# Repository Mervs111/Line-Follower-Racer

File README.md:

# Line Follower ESP32 + Block Programming

Proyek PjBL Semester 5: robot line follower edukasi yang murah tapi performanya bagus, dan bisa diprogram pakai
blok (user extension Mind+). Target lomba: IARC XII Smart Robotics (9–10/01/2027). Anggaran maks Rp1.000.000 (naik dari Rp900.000 pada 26/10/2026).

> **Untuk anggota kelompok:** baca bagian [Status terkini](#status-terkini-23102026) dan
> [Yang harus dilakukan](#yang-harus-dilakukan-berikutnya) dulu. Catatan kerja harian ada di
> [`docs/log-kerja.md`](docs/log-kerja.md); detail rancangan lengkap (pin map, keputusan, aturan) di
> [`CLAUDE.md`](CLAUDE.md).

## Status terkini (23/10/2026)

| Bagian | Status | Di mana |
|---|---|---|
| Charter & RAB | Charter sudah disesuaikan dengan rancangan terbaru. **RAB Rp937.390 (harga hasil validasi marketplace 27/10), sisa Rp62.610** dari batas Rp1.000.000 | `docs/charter.md`, `docs/Project_Charter_PJBL.docx` |
| Diagram (blok, wiring, arsitektur, flowchart) | Selesai, sudah sesuai rancangan 22/10 | tautan di bawah, `docs/wiring-diagram.html` |
| PCB sensor | **Rev B disetujui**: bentuk jangkar, lebar 95 mm, 12 QRE1113GR + mux CD74HC4067, DRC 0 | `hardware/sensor-garis/` (+ `REVISI.md`) |
| Skematik PCB utama | **Selesai**: 21 komponen, ERC 0, netlist dicek terhadap pin map | `hardware/pcb-utama/pcb-utama.kicad_sch`, PDF `pcb-utama-skematik.pdf` |
| Layout PCB utama | **Routing pertama selesai** (22/10): bentuk "mobil F1" 100 × 127 mm, semua net tersambung, GND pour 2 sisi. Masih ada 11 error DRC dari footprint Q1 dan SW1 (lihat di bawah) | `hardware/pcb-utama/` (+ `README.md`) |
| Mekanik | Model 3D **v16**: PCB sensor rev B + PCB utama F1, 0 tabrakan. Body 3D print belum masuk RAB | `mechanical/` |
| Firmware | **Belum mulai** (M0). `Pins.h` dan `platformio.ini` masih untuk ESP32-S3 lama | `firmware/` |
| Extension Mind+ | Belum mulai (M6) | `mindplus-ext/` |

### Lihat hasilnya (artifact claude.ai)

- Model 3D v16 (bisa diputar): https://claude.ai/artifact/C6BMXLgUPLJN5Aubm8uyx3
- Perbandingan opsi bentuk PCB utama: https://claude.ai/artifact/PYASQTHgLPKjVaxw33yyMZ
- Wiring diagram per blok: https://claude.ai/artifact/Enb11oGXVb5YkwQmU6DhJY
- Diagram blok sistem: https://claude.ai/artifact/VgPaH3FbRFSDaHB658YTcT
- Arsitektur sistem: https://claude.ai/artifact/9dNV7sB3TdaNBcSojbtzAa · Flowchart: https://claude.ai/artifact/EMfY1GGrPrx9etNHpKmhEi

Artifact bersifat privat. Kalau link tidak bisa dibuka, minta pemiliknya membagikan lewat menu Share. Render
gambar model juga ada di `mechanical/render/`.

## Yang harus dilakukan berikutnya

Urut dari yang paling mendesak. Batas waktu dari pedoman PjBL dan charter: desain mekanik selesai **minggu 8**,
PCB dipesan **paling lambat minggu 10**, prototipe jalan 3× berturut-turut untuk **G3 (minggu 10)**.

### 1. Keputusan kelompok (perlu dibahas dulu)

- [x] ~~Pangkas RAB Rp2.000~~: tidak perlu lagi, batas anggaran naik jadi Rp1.000.000 (26/10).
- [ ] **Ukuran PCB utama**: tetap 100 × 127 mm, atau dipadatkan (OLED ditumpuk di atas ESP32, hidung dipendekkan,
      resistor SMD; perkiraan 15–25 % lebih kecil). Mengganti 18650 dengan LiPo bisa membuat papan jauh lebih kecil,
      tapi bertentangan dengan alasan keselamatan di charter, jadi tanyakan dosen dulu.
- [ ] **Saklar SW1**: pad pemasangnya berjarak 0,25 mm dari pad lain (batas tempat cetak 0,254 mm). Pilihannya:
      pelanggaran ini dikecualikan di DRC, atau ganti saklar.
- [x] ~~Skid nilon~~: diganti **ball caster** (RAB 27/10). Model 3D v16 masih memakai skid, perlu diperbarui.

### 2. PCB utama (sampai siap pesan)

- [ ] Ganti footprint Q1 ke `Package_TO_SOT_THT:TO-92_Inline_Wide` di Eeschema, lalu F8 di PCB Editor. Jangan
      jalankan ulang `gen_sch_utama.py` karena UUID-nya acak dan akan mengacak penempatan.
- [ ] Rapikan jalur Q1 ↔ R3/R4/buzzer, jalur daya (BAT+ masih melintang miring di B.Cu), dan silkscreen yang bertumpuk.
- [ ] **Cocokkan footprint modul dengan modul yang dibeli** (ESP32 DevKit, TB6612, MP1584 di `hardware/ltm-lib/`).
      Ukur jarak pin modul asli pakai jangka sorong; footprint sekarang masih perkiraan.
- [ ] **Footprint ikut barang di RAB 27/10**: tombol SW2/SW3 → tactile 12×12 mm (sekarang `SW_PUSH_6mm`), konektor
      motor J2/J3 → JST XH 6 pin `B6B-XH-A` (sekarang JST PH 2,0). Kabel encoder N20 bawaan biasanya berkonektor
      PH 2,0, jadi ujung kabelnya perlu diganti housing XH.
- [ ] DRC 0 error → buat Gerber → pesan PCB utama **bersama PCB sensor** (ikuti `docs/aturan-cetak-pcb.md`).

### 3. Pembelian & mekanik

- [x] ~~Tautan toko~~: ada di `docs/charter.md` bagian 8 (27/10), kecuali mux WKH Electronic (menyusul).
- [ ] Koreksi spreadsheet RAB kelompok: baris mux masih modul CD74HC4067 kakarobot Rp35.000; yang dipakai IC
      CD74HC4067M SOP-24 dari WKH Electronic Rp20.000 (keputusan 27/10).
- [ ] Info printer 3D lab → body 3D print (cover, bumper, dudukan motor & baterai, sayap) masuk RAB atau tidak.
- [ ] Sinkronkan `docs/perhitungan-motor.md` dengan charter (≥ 0,5 m/s) dan roda Ø34.

### 4. Firmware (mulai sesudah komponen ada)

- [ ] Perbarui `firmware/lib/LineFollower/src/Pins.h` ke pin map ESP32 DevKit (tabel di `CLAUDE.md`) dan
      `platformio.ini` ke board ESP32 DevKit.
- [ ] Kerjakan milestone M0 → M7 berurutan (lihat [Progres firmware](#progres-firmware)). Tiap milestone dites di
      hardware dulu sebelum lanjut. Sementara PCB belum datang, tes di breadboard (pinjam lab).

### 5. Dokumen PjBL

- [ ] **Analisis bahaya (FMEA) ≥ 8 mode kegagalan** untuk G3 (minggu 7–8), belum ada di repo. Daftar risiko di
      charter bisa jadi titik awal.
- [ ] Logbook: konfirmasi ke pembimbing format mana yang dipakai (logbook perseorangan Lampiran C atau template
      departemen, mungkin keduanya). Isi `docs/logbook/logbook-utama.md` dengan kegiatan tim yang benar-benar
      terjadi; entri terakhir masih 02/10.
- [ ] Dokumen lama yang belum ikut rancangan terbaru: `docs/skematik-v1.md`, `docs/minsys-v1.md`,
      `docs/00-mulai-dari-sini.md` (masih ESP32-S3), `docs/gen_rab_pemeliharaan.py`.

## Rancangan singkat

| Bagian | Pilihan |
|---|---|
| MCU | ESP32 DevKit 30 pin (ESP32 biasa, CH340/CP2102), di socket di atas PCB utama |
| Sensor | 12× QRE1113GR + mux CD74HC4067 (SOIC-24) di PCB sensor bentuk jangkar, kabel JST XH 8 pin ke PCB utama |
| Driver motor | Modul TB6612FNG + motor N20 6V 500 RPM dengan encoder, roda Ø34 |
| Daya | 2× 18650 (2S) + BMS 2S + charger USB-C → buck MP1584 5 V |
| UI | OLED 0,96" I2C (bacaan sensor tampil sebagai bar), 2 tombol, buzzer aktif |
| Mekanik | Bentuk rendah gaya Ichiduino: PCB jadi sasis, body 3D print (cover, bumper, dudukan, sayap belakang) |

Arsitektur perangkat lunak 3 lapis:

1. **Library C++ `LineFollower`** (`firmware/lib/LineFollower/`): logika utama, ditulis dan dites duluan.
2. **Desain blok**: 1 blok = 1 fungsi library.
3. **Extension Mind+** (`mindplus-ext/`): blok menghasilkan kode C++ yang memanggil library, di-compile native
   sehingga loop PID tetap cepat.

## Struktur repo

```
├── CLAUDE.md        rancangan lengkap, pin map, riwayat keputusan, aturan kerja
├── firmware/        proyek PlatformIO (library LineFollower + program uji)
├── mindplus-ext/    extension Mind+
├── hardware/        KiCad: sensor-garis/ (PCB sensor rev B), pcb-utama/ (PCB utama baru), ltm-lib/ (footprint modul),
│                    tools/ (generator skematik/PCB, autoroute FreeRouting, MCP KiCad), ltm-main/ (v2 lama)
├── mechanical/      model 3D v16 (CadQuery, STEP, DXF, STL, render); v15 untuk perbandingan
├── docs/            charter, RAB, wiring diagram, diagram blok, aturan cetak PCB, logbook, log kerja
└── arsip/           file yang sudah digantikan rancangan terbaru
```

## Cara ikut mengerjakan

1. `git pull` dulu sebelum mulai, supaya dapat versi terbaru.
2. Buka file KiCad pakai **KiCad 10** (KiCad 8 tidak bisa membuka file versi ini).
3. Model 3D: buka file `.step` di `mechanical/v16/step/` (Fusion, Inventor, FreeCAD), atau lihat lewat link artifact.
4. Sesudah mengerjakan sesuatu, tulis ringkasannya di `docs/log-kerja.md` (per hari), lalu commit dengan pesan
   Bahasa Indonesia.

## Build firmware

```bash
cd firmware
pio run            # compile
pio run -t upload  # flash
pio device monitor # serial 115200
```

## Progres firmware

- [ ] M0: setup PlatformIO, serial jalan, tanda hidup lewat OLED/buzzer
- [ ] M1: driver motor + perintah serial `m <kiri> <kanan>`
- [ ] M2: baca 12 sensor mentah lewat mux, stream ke serial
- [ ] M3: kalibrasi + posisi + simpan/muat NVS
- [ ] M4: PID `follow()` + tuning lewat serial
- [ ] M5: persimpangan, tombol, buzzer, baterai + peringatan baterai lemah
- [ ] M6: extension Mind+
- [ ] M7: contoh program + panduan blok

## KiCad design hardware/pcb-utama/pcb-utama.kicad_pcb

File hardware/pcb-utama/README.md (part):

# PCB utama (baru, KiCad 10)

Proyek PCB utama pengganti `ltm-main/` (v2, 13/10). Skematik dibuat Claude atas permintaan user, layout
(penempatan, routing, DRC) oleh Claude lewat MCP KiCad + FreeRouting. Dibuat 22/10/2026 oleh `hardware/tools/gen_pcb_utama_awal.py`
(sekali jalan; `--paksa` menimpa .kicad_pcb dan .kicad_sch, jadi **jangan dijalankan lagi** sesudah user mulai
menggambar).

## Rev B (03/11/2026, konsep v17)

Rombak sesuai konsep v17 (`mechanical/konsep-v17/`, https://claude.ai/artifact/3zbiuQzc9YBamEs8NX5sxH): sasis jadi
skid plate 3D print, PCB utama **trapesium** sejajar skid plate (depan 62, belakang 87, panjang 58 mm; y robot 24–82),
4 lubang M3 di sayap, OLED dan tombol pindah ke **board interface** (`../board-interface/`) yang ditumpuk di atas.

- **Skematik rev B** (`gen_sch_utama.py --paksa`, 19 komponen, ERC 0, 22 pin ESP32 cocok tabel pin): J4 OLED, SW2/SW3,
  R6 dihapus; **J6** socket 1×6 ke board interface (1 +3V3, 2 GND, 3 SDA, 4 SCL, 5 BTN = GPIO34, 6 AUX = GPIO35);
  R5 10k tetap jadi pull-up BTN; **C2** 100 nF di VBAT_SENSE; J2/J3 **JST XH 6 pin**; Q1 **TO-92 Inline Wide**.
  Rev A disimpan di riwayat git (commit sebelum 03/11).
- **Footprint `ltm:MP1584_Module` diperbarui** (03/11) dari 3 foto listing CNC Store (miring, sisi atas, sisi bawah
  berlabel): 8 lubang, 2 per terminal jarak 2,54, kolom ±9,35, y ±4,55 / ±7,09. Dilihat dari sisi komponen (SS34 kiri
  atas, induktor kanan): **IN kiri, OUT kanan, − di atas, + di bawah** (pad kotak = +, sama dengan modul). Pad 1–4 =
  IN+, IN−, OUT+, OUT− (simbol tidak berubah). Silkscreen +/−/IN/OUT ditambahkan. Masih "UKUR ULANG" (±0,2 mm
  dari foto). Footprint di `.kicad_pcb` baru ikut setelah Tools → Update Footprints from Library.

### Layout rev B (04/11/2026)

Dibuat dari file oleh `hardware/tools/gen_pcb_utama_v17.py` (outline, penempatan, silkscreen, pour) + FreeRouting
2.1 (langkah lengkap: `hardware/tools/autoroute/README.md` bagian "Rev B"). Render: `render-atas.png`,
`render-bawah.png` (footprint `ltm` belum punya model 3D, jadi ESP32/TB6612/MP1584 tidak tergambar).

- **Outline** trapesium 86,6 / 62 × 58 mm (y robot 24–82), sudut R4, sisi miring sejajar skid plate. Lubang M3 di
  (±38,5; 29) dan (±32,5; 56).
- **Penempatan** (koordinat robot; footprint pustaka KiCad diukur dari pin 1):

| Blok | Posisi | Catatan |
|---|---|---|
| J2 motor kiri / J1 baterai / J3 motor kanan | baris belakang, y 28,6 (pin 1 x −31,9 / −1,25 / 19,4) | JST XH, label di dalam badan konektor |
| R1/R2 pembagi baterai, C1 elko | (−15,2; 26,2 / 29,6), (6,7; 28,1) | C1 di antara J1 dan J3, dekat VM TB6612 |
| SW1 saklar | tepi kiri (−37; 40,5), **tuas keluar ke kiri** | jalur VBAT semua di sisi kiri |
| U1 ESP32 DevKit | tengah (−3,5; 46,15), diputar −90° | USB ke kiri, antena ke kanan; **tanpa tembaga** di x 19–36,6, y 26,5–55,7 |
| U2 TB6612 | di bawah ESP32, (−10,75; 46,05) | disolder rendah, ESP32 di socket 8,5 mm di atasnya |
| R3, R4, Q1, R5, C2 | di bawah ESP32, kanan TB6612 (x 0,9 dan 12) | rendah (≤ 5 mm) |
| U3 MP1584 | kiri depan (−18,9; 70,5) | IN kiri, OUT kanan |
| D1, J6, J5 | (4,16; 72), pin 1 J6 (−5,6; 67,5), pin 1 J5 (13; 77,8) diputar 180° | J6 tepat di bawah J1 board interface |
| BZ1 buzzer | kanan depan (20,7; 67,5) | |

- **Beda dari gambar konsep v17**: SW1 di tepi kiri (konsep: depan, tuas ke kanan), D1 di depan dekat MP1584
  (konsep: belakang), J6 di tengah (konsep: x 2–17, y 73–75,5). Board interface jadi 46 × 36 mm (konsep 46 × 32,
  ditambah 4 lubang M2), tetap jauh dari holder baterai (y ≤ 21).
- **Routing**: 304 segmen, 17 via, panjang total ±1,41 m. Lebar: VBAT/BAT+ 1,0; motor, +5V, +5V_BUCK 0,8;
  +3V3/GND 0,5; sinyal 0,3 mm. GND pour F.Cu + B.Cu (jarak 0,5, tebal minimum 0,35). DSN + SES di `routing/`.
- **DRC** (`kicad-cli pcb drc --schematic-parity`): **0 error, 0 unconnected, cocok dengan skematik**. Sisa
  1 warning: SW1 tidak sama dengan pustaka. Pad pemasangnya sengaja dikecilkan (2,0 × 3,3 mm, `PAD_FIX`) supaya
  jaraknya ke kaki 1/3 dan tepi papan lolos aturan cetak, jadi **jangan "Update Footprints from Library" untuk SW1**.
- **Aturan tambahan** `pcb-utama.kicad_dru`: courtyard U1 boleh menumpuk komponen rendah di bawahnya; pad GND Q1 dan
  J6 cukup 1 spoke per layer (terkepung jalur, tersambung di dua layer, arus kecil).
- **Masih terbuka**:
  - Footprint MP1584 bertanda "UKUR ULANG". Ukur modulnya saat datang.
  - Sisi bawah ESP32 DevKit belum dicek (kalau CH340 di bawah, TB6612 tidak muat).
  - Cara pasang dan panjang header ke board interface (lihat `../board-interface/README.md`).
- Dibuat dari file saat KiCad mungkin masih membuka layout lama. **Tutup PCB Editor tanpa menyimpan** (atau
  File → Revert) sebelum membuka file ini, supaya layout rev A tidak tersimpan menimpa.

## Isi awal (rev A, 22/10; bagian ini dan di bawahnya riwayat, layout rev A ada di riwayat git)

| File | Isi |
|---|---|
| `pcb-utama.kicad_pro` | salinan setting PCB sensor (aturan cetak 21/10, net class), nama diganti |
| `pcb-utama.kicad_sch` | **skematik lengkap** (22/10, dibuat `hardware/tools/gen_sch_utama.py`): 21 komponen, ERC 0, netlist dicek terhadap tabel pin CLAUDE.md. PDF: `pcb-utama-skematik.pdf` |
| `pcb-utama.kicad_pcb` | outline + lubang + gambar bantu, **21 footprint ditempatkan dan dirouting** (22/10, lihat "Layout") |
| `sym-lib-table`, `fp-lib-table` | library `ltm` di `../ltm-lib` (ESP32 DevKit, modul TB6612, MP1584). Footprint ini sementara: cocokkan ukurannya dengan modul yang dibeli |

Cek awal: `kicad-cli pcb drc` 0 error, `kicad-cli sch erc` 0 error.

## Layout (22/10/2026, routing pertama)

- Penempatan mengikuti model 3D v16. ESP32 (U1) di (196,5; 141,9), diputar −90° (pin 1 di depan-kanan), digeser
  3,5 mm ke kiri dari tengah karena footprint DevKit lebih panjang di sisi antena (kalau tidak, menabrak TB6612).
  TB6612 (U2) diputar −90°: baris daya (VM, motor) menghadap belakang ke J2/J3, baris logika ke depan.
- Routing: FreeRouting 2.1.0 lewat `hardware/tools/autoroute/` (README di sana), 339 segmen + 15 via. Lebar: VBAT/BAT+
  1,0 mm; motor, +5V, +5V_BUCK 0,8 mm; +3V3/GND 0,5 mm; sinyal 0,3 mm. GND pour F.Cu + B.Cu, jarak 0,5 mm.
- DRC: **0 unconnected**; 11 error tersisa semuanya dari footprint pustaka, belum diperbaiki:
  - **Q1 `TO-92_Inline`** (pitch 1,27): clearance 0,22 dan annular 0,15 di bawah aturan cetak. Rencana: ganti
    footprint di skematik ke `Package_TO_SOT_THT:TO-92_Inline_Wide` (lewat Eeschema, lalu F8; generator skematik
    memakai UUID acak, jadi jangan dibuat ulang), lalu rapikan jalur Q1 ↔ R3/R4/BZ1.
  - **SW1** (OS102011MA1Q): pad pemasang tanpa net berjarak 0,25 mm dari pad 1/3 (batas cetak 0,254). Menunggu
    keputusan user: kecualikan di DRC atau ganti saklar.
- Hasil autorouter belum dirapikan (BAT+ melintang miring di B.Cu dari J1 ke SW1, beberapa jalur berbelok-belok).
  Warning silkscreen (referensi bertumpuk) juga belum dibereskan.

## Koordinat (sama dengan proyek PCB sensor)

X KiCad = 200 + x robot, Y KiCad = 180,55 − y robot. Robot: x ke kanan, y maju, 0,0 = tengah poros roda.
Karena sama, lubang H1/H2 PCB sensor (KiCad (195,25; 95) dan (204,75; 95)) jatuh tepat di lubang PCB utama, dan
outline PCB sensor rev B terlihat di lapisan **User.Comments** sebagai acuan.

## Bentuk dan lubang (dari model 3D v16)

- Outline: bentuk **"mobil F1"** (dipilih user 22/10, 100 × 127 mm): sidepod lebar di samping (x ±50, y 23,5–54),
  pinggang menyempit di antara roda (x ±37), lalu hidung panjang (x ±27) ke PCB sensor. Tiap sudut punya jari-jari
  sendiri (3–10 mm). Sumber satu-satunya: `MAIN_R` di `mechanical/cadquery/ltm_v16.py` (titik x, y, jari-jari
  setengah kanan; kiri dicerminkan). Perbandingan 3 opsi: https://claude.ai/artifact/PYASQTHgLPKjVaxw33yyMZ
- 4 lubang M3 tiang dudukan motor + baterai di robot (±33; ±20).
- 2 lubang M3 PCB sensor H1/H2 di robot (±4,75; 85,55).
- 2 celah piringan encoder motor (X 10,2–13,9 kiri dan kanan, Y −6,6..6,6).

## Gambar bantu penempatan (User.Drawings)

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
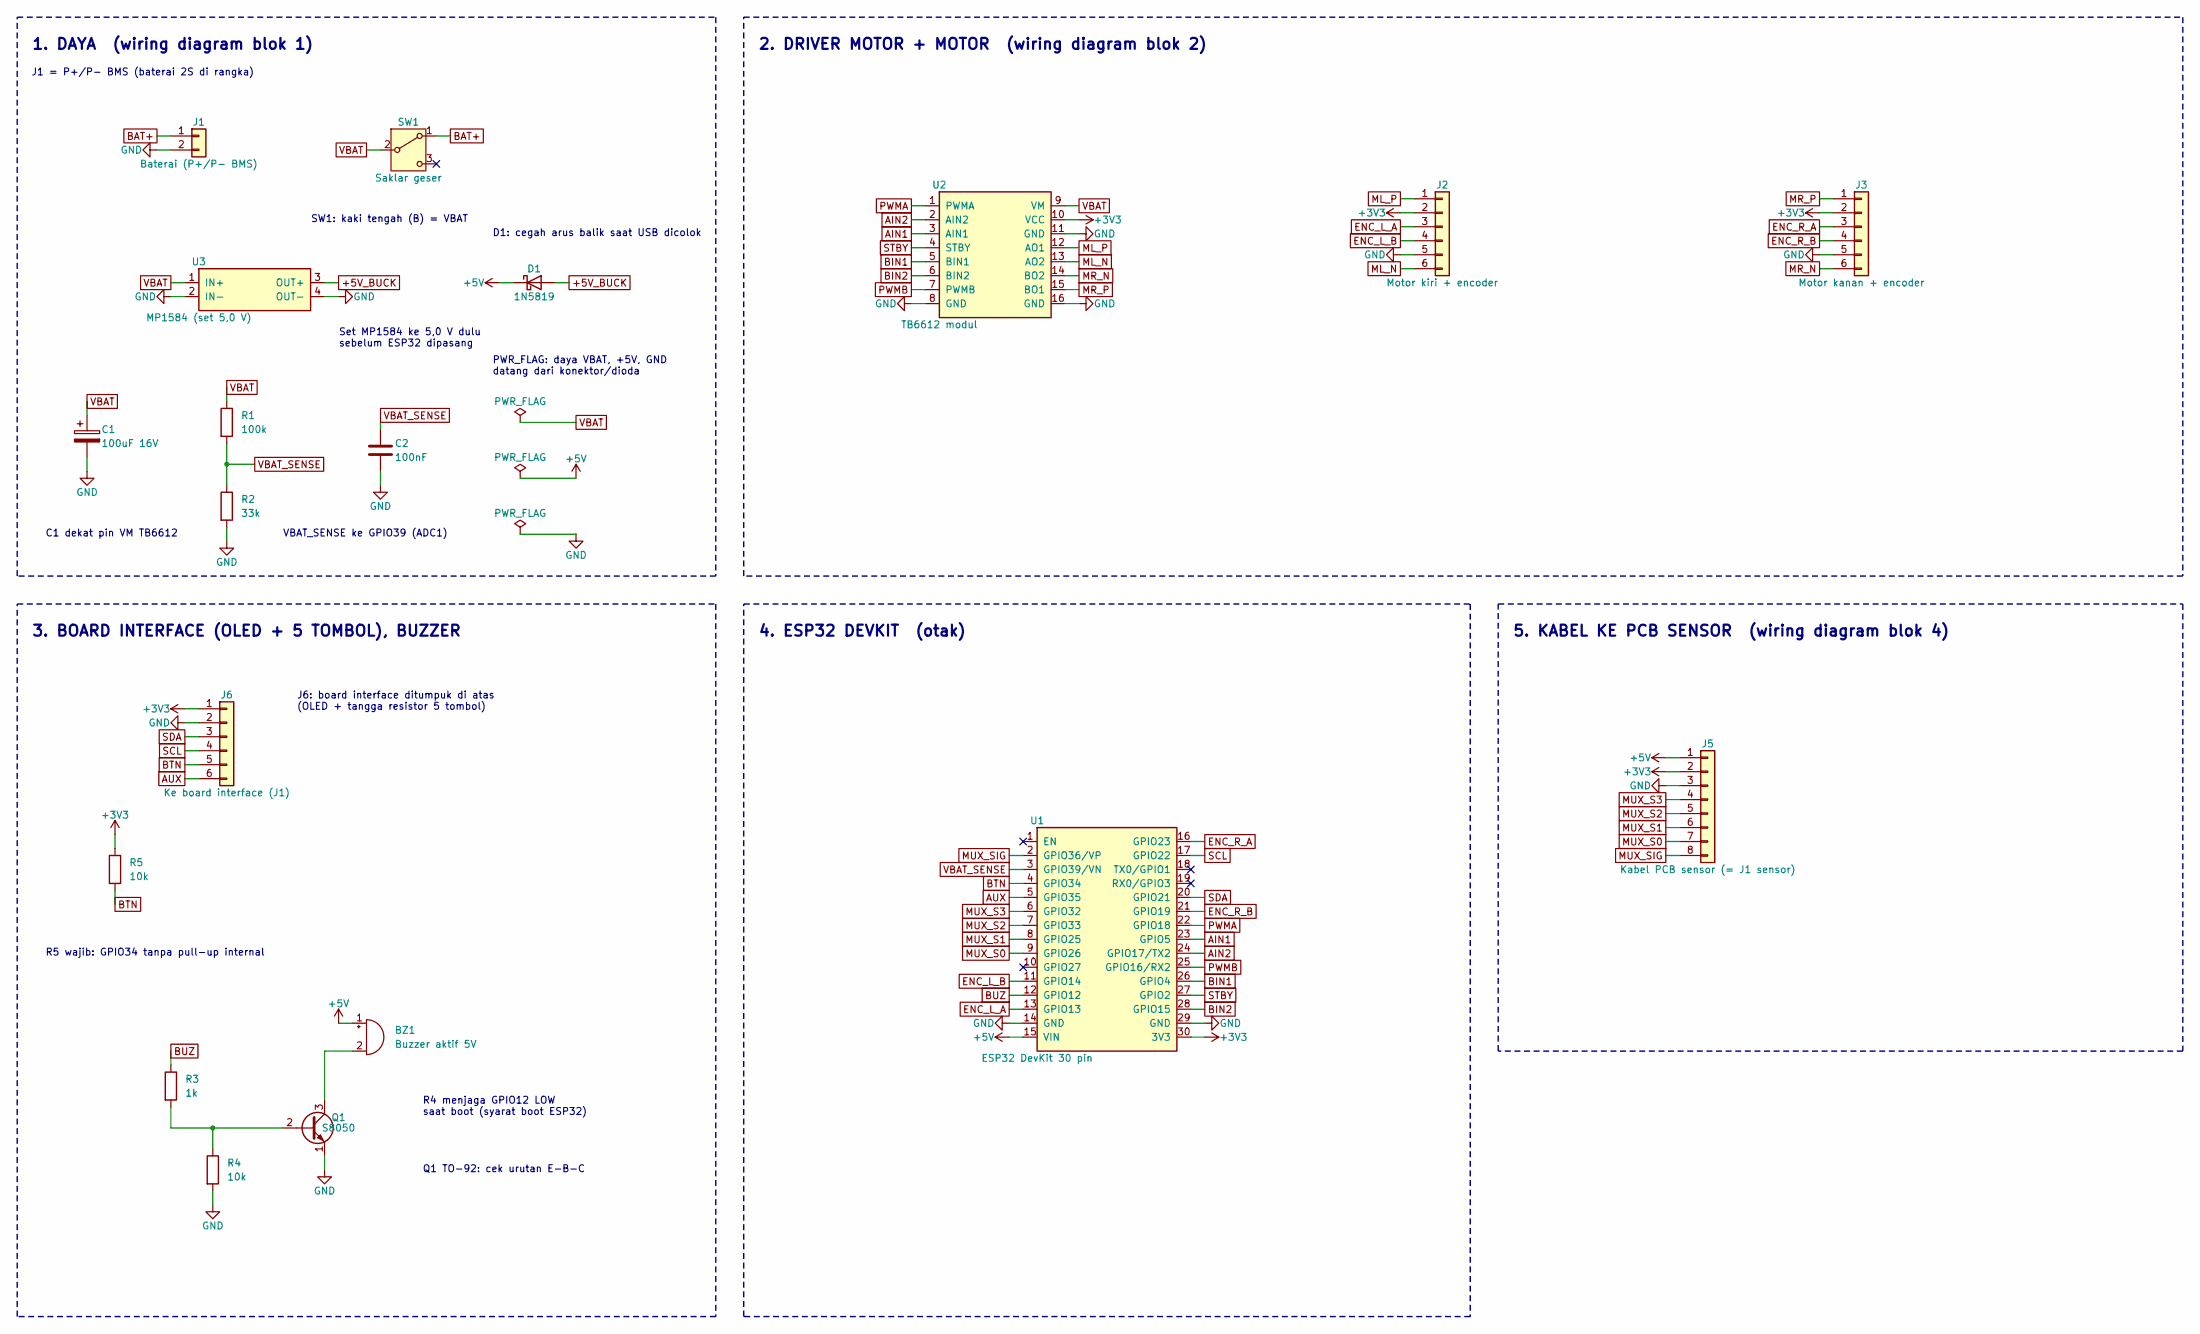
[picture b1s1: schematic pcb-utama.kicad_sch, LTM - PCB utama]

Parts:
BZ1: Buzzer aktif 5V; Buzzer_12x9.5RM7.6
C1: 100uF 16V; CP_Radial_D6.3mm_P2.50mm
C2: 100nF; C_Disc_D5.0mm_W2.5mm_P5.00mm
D1: 1N5819; D_DO-41_SOD81_P10.16mm_Horizontal
J1: Baterai (P+/P- BMS); JST_XH_B2B-XH-A_1x02_P2.50mm_Vertical
J2: Motor kiri + encoder; JST_XH_B6B-XH-A_1x06_P2.50mm_Vertical
J3: Motor kanan + encoder; JST_XH_B6B-XH-A_1x06_P2.50mm_Vertical
J5: Kabel PCB sensor (= J1 sensor); JST_XH_B8B-XH-A_1x08_P2.50mm_Vertical
J6: Ke board interface (J1); PinSocket_1x06_P2.54mm_Vertical
Q1: S8050; TO-92_Inline_Wide
R1: 100k; R_Axial_DIN0207_L6.3mm_D2.5mm_P7.62mm_Horizontal
R2: 33k; R_Axial_DIN0207_L6.3mm_D2.5mm_P7.62mm_Horizontal
R3: 1k; R_Axial_DIN0207_L6.3mm_D2.5mm_P7.62mm_Horizontal
R4, R5: 10k; R_Axial_DIN0207_L6.3mm_D2.5mm_P7.62mm_Horizontal
SW1: Saklar geser; SW_Slide_SPDT_Angled_CK_OS102011MA1Q
U1: ESP32 DevKit 30 pin; ESP32_DevKit_30P_W25.4
U2: TB6612 modul; TB6612_Module_2x8_W15.24
U3: MP1584 (set 5,0 V); MP1584_Module

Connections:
+3V3: J2.2, J3.2, J5.2, J6.1, R5.1, U1.30 (3V3), U2.10 (VCC)
+5V: BZ1.1 (+), D1.1 (K), J5.1, U1.15 (VIN)
+5V_BUCK: D1.2 (A), U3.3 (OUT+)
AIN1: U1.23 (GPIO5), U2.3 (AIN1)
AIN2: U1.24 (GPIO17/TX2), U2.2 (AIN2)
AUX: J6.6, U1.5 (GPIO35)
BAT+: J1.1, SW1.1 (A)
BIN1: U1.26 (GPIO4), U2.5 (BIN1)
BIN2: U1.28 (GPIO15), U2.6 (BIN2)
BTN: J6.5, R5.2, U1.4 (GPIO34)
BUZ: R3.1, U1.12 (GPIO12)
ENC_L_A: J2.3, U1.13 (GPIO13)
ENC_L_B: J2.4, U1.11 (GPIO14)
ENC_R_A: J3.3, U1.16 (GPIO23)
ENC_R_B: J3.4, U1.21 (GPIO19)
GND: C1.2, C2.2, J1.2, J2.5, J3.5, J5.3, J6.2, Q1.1 (E), R2.2, R4.2, U1.14 (GND), U1.29 (GND), U2.8 (GND), U2.11 (GND), U2.16 (GND), U3.2 (IN-), U3.4 (OUT-)
ML_N: J2.6, U2.13 (AO2)
ML_P: J2.1, U2.12 (AO1)
MR_N: J3.6, U2.14 (BO2)
MR_P: J3.1, U2.15 (BO1)
MUX_S0: J5.7, U1.9 (GPIO26)
MUX_S1: J5.6, U1.8 (GPIO25)
MUX_S2: J5.5, U1.7 (GPIO33)
MUX_S3: J5.4, U1.6 (GPIO32)
MUX_SIG: J5.8, U1.2 (GPIO36/VP)
unnamed: BZ1.2 (-), Q1.3 (C)
unnamed: Q1.2 (B), R3.2, R4.1
PWMA: U1.22 (GPIO18), U2.1 (PWMA)
PWMB: U1.25 (GPIO16/RX2), U2.7 (PWMB)
SCL: J6.4, U1.17 (GPIO22)
SDA: J6.3, U1.20 (GPIO21)
STBY: U1.27 (GPIO2), U2.4 (STBY)
VBAT: C1.1, R1.1, SW1.2 (B), U2.9 (VM), U3.1 (IN+)
VBAT_SENSE: C2.1, R1.2, R2.1, U1.3 (GPIO39/VN)

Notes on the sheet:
1. DAYA (wiring diagram blok 1)
PWR_FLAG: daya VBAT, +5V, GND datang dari konektor/dioda
J1 = P+/P- BMS (baterai 2S di rangka)
SW1: kaki tengah (B) = VBAT
Set MP1584 ke 5,0 V dulu sebelum ESP32 dipasang
D1: cegah arus balik saat USB dicolok
C1 dekat pin VM TB6612
VBAT_SENSE ke GPIO39 (ADC1)
2. DRIVER MOTOR + MOTOR (wiring diagram blok 2)
3. BOARD INTERFACE (OLED + 5 TOMBOL), BUZZER
J6: board interface ditumpuk di atas (OLED + tangga resistor 5 tombol)
R5 wajib: GPIO34 tanpa pull-up internal
R4 menjaga GPIO12 LOW saat boot (syarat boot ESP32)
Q1 TO-92: cek urutan E-B-C
4. ESP32 DEVKIT (otak)
5. KABEL KE PCB SENSOR (wiring diagram blok 4)

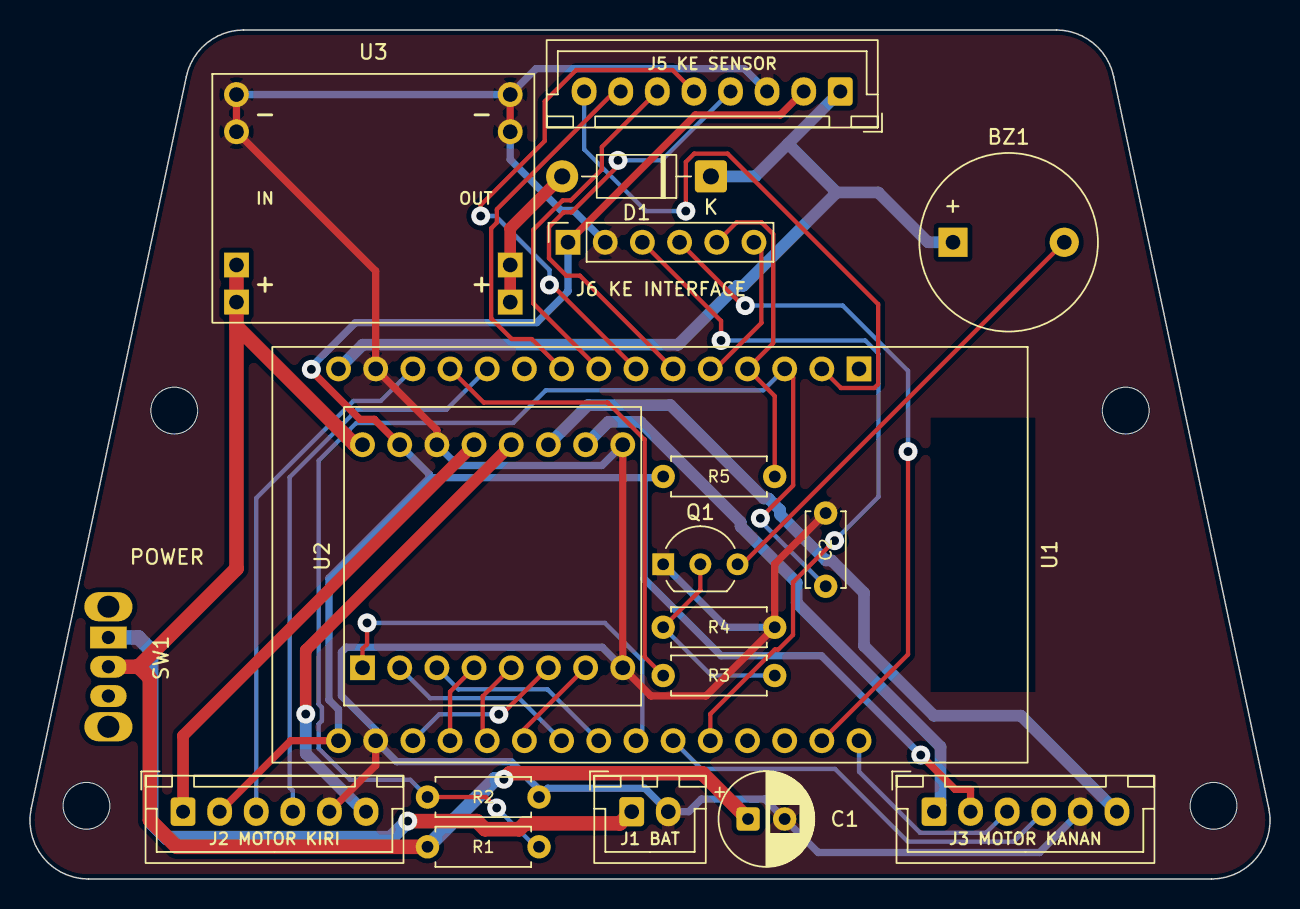
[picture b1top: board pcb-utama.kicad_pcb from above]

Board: 2 copper layers, 84.7 x 58.0 mm, 23 parts (0 on the bottom side), 34 nets.

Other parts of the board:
H1, H2, H3, H4: M3; MountingHole_3.2mm_M3

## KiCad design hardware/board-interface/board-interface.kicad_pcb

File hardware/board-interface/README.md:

# Board interface (KiCad 10)

Board kecil yang ditumpuk di atas PCB utama (konsep v17, 03/11/2026): OLED 0,96 inci di socket di tengah, 5 tombol
6×6 mengapit untuk menu OLED (kiri: atas, bawah; kanan: kembali, OK, lanjut). Ukuran konsep 46 × 32 mm, PCB jadi 46 × 36 mm (ditambah lubang M2).

| File | Isi |
|---|---|
| `board-interface.kicad_pro` | salinan setting PCB utama (aturan cetak, net class) |
| `board-interface.kicad_sch` | skematik rev A dari `hardware/tools/gen_sch_interface.py`, 13 komponen, ERC 0. PDF: `board-interface-skematik.pdf` |

**Tangga resistor**: tombol k menghubungkan BTN (GPIO34) ke GND lewat Rk; pull-up 10k (R5) ada di PCB utama.

| Tombol | Rk | Tegangan BTN |
|---|---|---|
| SW1 Atas | 1k | 0,30 V |
| SW2 Bawah | 3,9k | 0,93 V |
| SW3 Kembali | 8,2k | 1,49 V |
| SW4 OK | 18k | 2,12 V |
| SW5 Lanjut | 39k | 2,63 V |
| tidak ditekan | – | 3,3 V |

Hanya satu tombol terbaca dalam satu waktu (cukup untuk menu). C1 100 nF di BTN meredam derau.

**J1** = header 1×6 (urutan sama dengan J6 PCB utama: +3V3, GND, SDA, SCL, BTN, AUX tidak dipakai). Jarak antar board
±16 mm (atas PCB utama z 16,6 → bawah board interface z 33). Socket J6 8,5 mm + header biasa (6 mm masuk) tidak
sampai, jadi perlu **header pin panjang** atau spacer. Cara pasang board ini (dudukan) **belum diputuskan**.

## PCB rev A (04/11/2026)

Dibuat oleh `hardware/tools/gen_pcb_interface.py` (penempatan, silkscreen, pour) + `hardware/tools/autoroute/sisa.py`
(routing, GND lewat pour). Render: `render-atas.png`, `render-bawah.png`.

- **46 × 36 mm** (x robot −27..19, y 43..79), sudut R2, **4 lubang M2** di pojok (x −24,5 / 16,5, y 45,5 / 76,5),
  untuk dudukan apa pun yang dipilih nanti (jembatan 3D print ke lubang M3 PCB utama, spacer, atau cover).
- OLED di socket J2 (tengah atas; modulnya 27,3 × 27,8 mm menutupi tangga resistor). Tombol: kiri ATAS/BAWAH, kanan
  KEMBALI/OK/LANJUT. R1/R2 di kiri, R3–R5 di kanan, dekat tombolnya.
- **J1 dipasang di sisi bawah** (menghadap PCB utama). Pin 1–6 di x −5,6 … 7,1, y 67,5, **sama persis dengan J6 PCB
  utama** (dicek dari kedua file .kicad_pcb).
- Routing 2 layer tanpa via, GND pour F.Cu + B.Cu. DRC: **0 error, 0 warning, 0 unconnected, cocok dengan
  skematik**. Aturan tambahan `board-interface.kicad_dru`: courtyard tombol 6×6 dan lubang M2 boleh bersinggungan
  (badan tombol berjarak 3 mm, tembaga ke lubang ≥ 1,1 mm).

Buat ulang (sesudah skematik berubah):

```bash
KPY="/c/Program Files/KiCad/10.0/bin/python.exe"; K="/c/Program Files/KiCad/10.0/bin/kicad-cli.exe"; I=hardware/board-interface
"$K" sch export netlist -o if.net $I/board-interface.kicad_sch
"$KPY" hardware/tools/gen_pcb_interface.py if.net hardware/pcb-utama/pcb-utama.kicad_pcb $I/board-interface.kicad_pcb
"$K" pcb drc --severity-all --format json -o drc.json $I/board-interface.kicad_pcb
"$KPY" hardware/tools/autoroute/sisa.py $I/board-interface.kicad_pcb drc.json GND   # ulangi sampai 0 (selain GND)
"$KPY" hardware/tools/gen_pcb_interface.py pour $I/board-interface.kicad_pcb
```

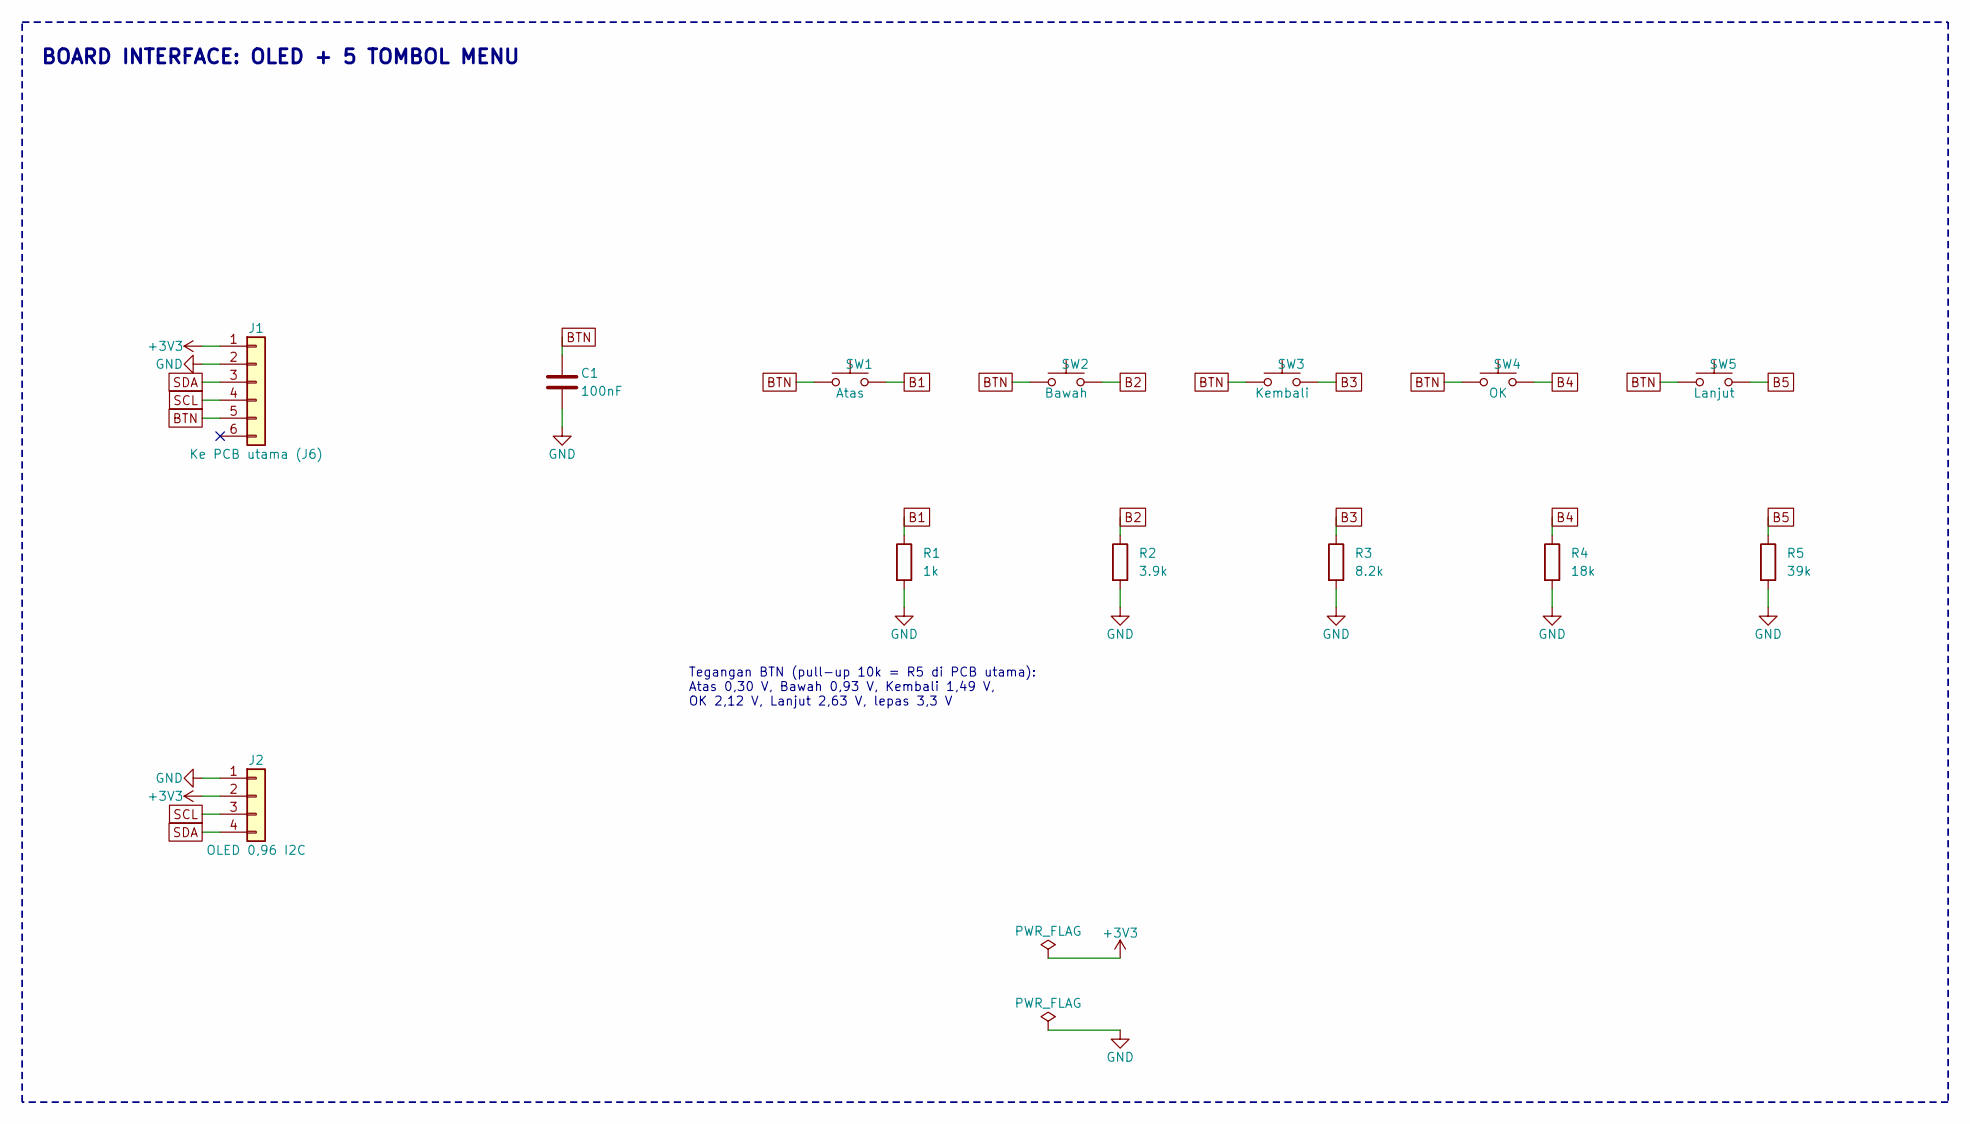
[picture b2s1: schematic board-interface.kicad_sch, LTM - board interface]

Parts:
C1: 100nF; C_Disc_D5.0mm_W2.5mm_P5.00mm
J1: Ke PCB utama (J6); PinHeader_1x06_P2.54mm_Vertical
J2: OLED 0,96 I2C; PinSocket_1x04_P2.54mm_Vertical
R1: 1k; R_Axial_DIN0207_L6.3mm_D2.5mm_P7.62mm_Horizontal
R2: 3.9k; R_Axial_DIN0207_L6.3mm_D2.5mm_P7.62mm_Horizontal
R3: 8.2k; R_Axial_DIN0207_L6.3mm_D2.5mm_P7.62mm_Horizontal
R4: 18k; R_Axial_DIN0207_L6.3mm_D2.5mm_P7.62mm_Horizontal
R5: 39k; R_Axial_DIN0207_L6.3mm_D2.5mm_P7.62mm_Horizontal
SW1: Atas; SW_PUSH_6mm
SW2: Bawah; SW_PUSH_6mm
SW3: Kembali; SW_PUSH_6mm
SW4: OK; SW_PUSH_6mm
SW5: Lanjut; SW_PUSH_6mm

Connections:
+3V3: J1.1, J2.2
B1: R1.1, SW1.2
B2: R2.1, SW2.2
B3: R3.1, SW3.2
B4: R4.1, SW4.2
B5: R5.1, SW5.2
BTN: C1.1, J1.5, SW1.1, SW2.1, SW3.1, SW4.1, SW5.1
GND: C1.2, J1.2, J2.1, R1.2, R2.2, R3.2, R4.2, R5.2
SCL: J1.4, J2.3
SDA: J1.3, J2.4

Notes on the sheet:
BOARD INTERFACE: OLED + 5 TOMBOL MENU
Tegangan BTN (pull-up 10k = R5 di PCB utama): Atas 0,30 V, Bawah 0,93 V, Kembali 1,49 V, OK 2,12 V, Lanjut 2,63 V, lepas 3,3 V

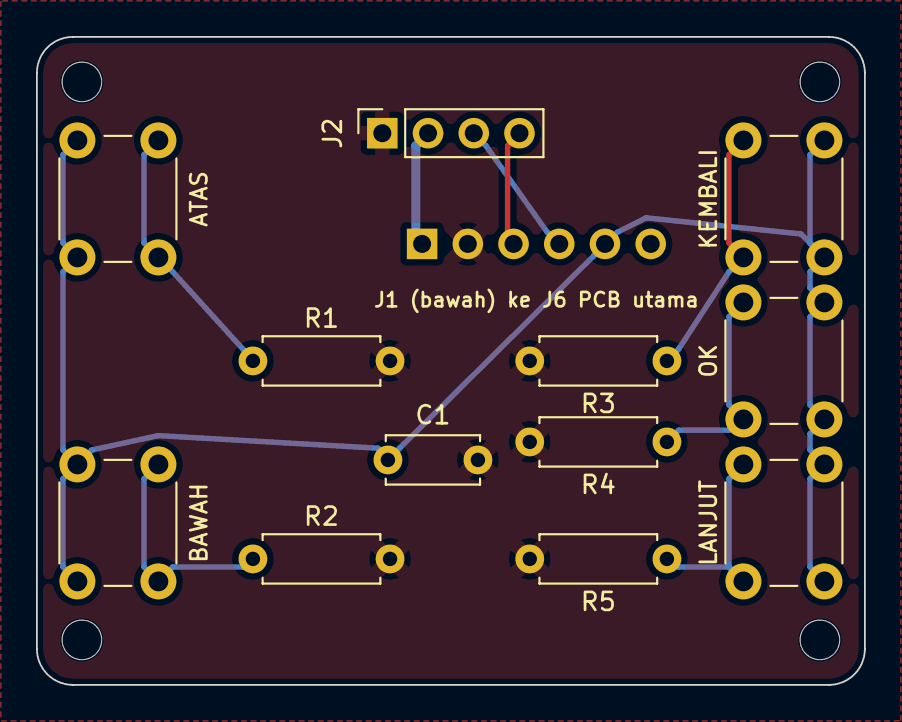
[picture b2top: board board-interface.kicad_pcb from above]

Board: 2 copper layers, 46.0 x 36.0 mm, 17 parts (1 on the bottom side), 10 nets.

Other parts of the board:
H1, H2, H3, H4: M2; MountingHole_2.2mm_M2

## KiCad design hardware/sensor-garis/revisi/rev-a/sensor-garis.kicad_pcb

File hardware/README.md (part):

# Hardware — Robot Line Tracer Micro (KiCad)

Starter proyek KiCad dibuat 11/10/2026 dari `docs/skematik-v1.md`, layout PCB v1-draft menyusul di hari yang
sama. **PCB utama v2 (13/10/2026)**: disederhanakan dan ditata ulang supaya gampang diakses untuk edukasi. Format KiCad 7, bisa dibuka KiCad 7, 8, atau 9 (KiCad 8/9 menawarkan upgrade format saat disimpan:
pilih **Ya**).

```
hardware/
├── ltm-lib/
│   ├── ltm.kicad_sym        symbol: ESP32_DevKit_30, TB6612_Module, MP1584_Module, ITR20001
│   └── ltm.pretty/          footprint SEMENTARA (lihat checklist)
├── pcb-utama/               **PCB utama baru** (KiCad 10, 22/10): outline + gambar bantu, skematik digambar user
├── ltm-main/                PCB utama v2 lama (13/10, kabel pita IDC), tidak dipakai lagi
├── sensor-garis/            **PCB sensor terbaru buatan user** (KiCad 10, 12 QRE1113GR + CD74HC4067);
│                            riwayat revisi di sensor-garis/REVISI.md
├── outline/                 outline simetris PCB sensor (DXF) dari layout user
├── aturan-cetak-template/   setting KiCad sesuai aturan cetak 21/10 (impor lewat Board Setup)
├── render/                  gambar PCB (atas/bawah + rakitan) untuk laporan/PPT
├── ltm-main.pdf             cetakan skematik PCB utama
└── tools/                   generator (JANGAN dijalankan ulang tanpa alasan: menimpa file) + kicad-mcp/
```

**22/10/2026:** PCB sensor v2 hasil generator (16 ITR20001 + MCP23017, `ltm-sensor/`) sudah usang dan dipindah ke
`arsip/hardware/`. Bagian "PCB sensor v2" di bawah hanya untuk riwayat; generator (`tools/`) masih menulis ke
`hardware/ltm-sensor/` kalau dijalankan ulang.

Library `ltm` sudah terdaftar di tiap proyek (`sym-lib-table`, `fp-lib-table`), tidak perlu ditambah manual.
Symbol dan footprint standar (R, C, konektor, power) memakai library bawaan KiCad.

## Isi skematik

- **PCB utama v2** (25 komponen, semua kaki tembus): daya (J1 baterai, SW1, MP1584, dioda 1N5819, elko
  100 µF, pembagi 100k/33k), ESP32 DevKit 30 pin, TB6612 + 2 konektor motor JST PH 6 pin, OLED, tombol A/B
  (+ pull-up R5/R6), buzzer + S8050, J5 box header IDC 2×6 ke kabel pita PCB sensor, 4 lubang M3. Dibanding v1, C2–C6 (100 nF/10 µF) dan R5–R8 (pull-up
  encoder) dibuang: modul TB6612, MP1584, dan ESP32 sudah punya kapasitor sendiri, dan encoder memakai
  pull-up internal ESP32 (`INPUT_PULLUP`).
- **PCB sensor v2** (82 komponen): 16× ITR20001 (LED IR seri berdua, 8× R 120 Ω), 16× pull-up 10k, modul
  mux CD74HC4067, MCP23017 + 16 LED indikator 0805 + 16× R 330 Ω, MOSFET AO3400 pengatur LED IR, box header
  IDC 2×6, 2 lubang M3 untuk dudukan.
- Sambungan memakai **net label** (nama sama = tersambung). Simbol GND/+5V/+3V3 = net daya global.
- `PWR_FLAG` dipasang supaya ERC tidak protes "power pin not driven".
- Netlist hasil ekspor KiCad sudah dicek otomatis terhadap `docs/skematik-v1.md`: 104 pin (utama) dan
  247 pin (sensor) cocok; pin sengaja tidak dipakai diberi tanda X (EN, TX0, RX0, kaki saklar ke-3,
  NC/INTA/INTB MCP23017).
- **Aturan cetak (tempat cetak user):** jalur minimal 0,8 mm (daya 1,2 mm); jarak antar tembaga 0,5 mm dan via
  1,6/0,8 mm = asumsi aman, **cek ke tempat cetak**. Nilainya di konstanta `FAB` (`tools/gen_pcb.py`).

## Layout PCB v2 (13/10/2026)

| | PCB utama v2 | PCB sensor v2 |
|---|---|---|
| Ukuran | 94 × 84 mm (siluet roket, sama dengan model mekanik v12) | 110 × 51 mm (batang lurus) |
| Lapisan | 2 layer, 1,6 mm | 2 layer, 1,6 mm |
| Jalur | 441 segmen, 41 via, semua ≥ 0,8 mm | 642 segmen, 56 via, semua ≥ 0,8 mm |
| Pour GND | atas + bawah (kecuali di bawah antena ESP32) | atas + bawah |
| DRC (KiCad 7.0.11) | 0 pelanggaran, 0 belum tersambung | 0 pelanggaran, 0 belum tersambung |

Cara lihat: buka `.kicad_pro` → **PCB Editor**. Tampilan 3D: **View › 3D Viewer** (Alt+3); modul ESP32,
TB6612, MP1584, ITR20001 belum punya model 3D (hanya kotak footprint). Gambar siap pakai ada di `render/`.

Penempatan komponen memakai koordinat model mekanik v12 (`mechanical/`), jadi
posisi modul, tombol, buzzer, konektor, dan sensor sama dengan model 3D. Jalur dibuat otomatis dengan
FreeRouting lalu dicek DRC.

### Susunan PCB utama v2 (dilihat dari atas, depan = arah maju)

| Blok (kotak silkscreen) | Isi | Posisi |
|---|---|---|
| OTAK | ESP32 DevKit di socket female | tengah-kiri, di depan dudukan baterai; USB menghadap ke kiri |
| LAYAR | OLED 1.3" di socket | kanan; header di sisi depan |
| DRIVER MOTOR | TB6612 di socket + C1 | tengah depan |
| SUARA | buzzer, Q1, R3, R4 | kiri depan |
| DAYA | MP1584, D1, R1/R2 (+ J1, SW1 di tepi kanan) | di bawah dudukan baterai |
| Tombol A/B (+ R5/R6), J5 kabel pita | | hidung |

Di depan kanan ada peta **ALUR DAYA** (BATERAI → SAKLAR → BUCK 5V → ESP32 + SENSOR, cabang ke MOTOR), tetap
terlihat setelah robot dirakit. Nama blok yang ada di bawah modul terbaca saat modulnya dicabut.

### Hal penting saat merakit

1. **Sambungan antar papan: kabel pita 12 pin.** J5 (PCB utama, hidung) dan J1 (PCB sensor, kanan belakang)
   = box header IDC 2×6 berkunci; kabel pita + 2 konektor IDC female, lurus pin n ke pin n (generator mengecek
   net tiap pin sama). PCB sensor dibaut ke 2 lengan dudukan 3D print: dari atas lewat H3/H4 PCB utama, dari
   bawah lewat H1/H2 PCB sensor (lihat `mechanical/`).
2. **Modul di socket.** ESP32 (2× socket female 1×15), TB6612 (2× 1×8), dan OLED (1×4) dipasang di socket
   header female ±8,5 mm, jadi bisa dicabut kalau rusak atau untuk ditunjukkan ke siswa. Modul memakai pin
   header male bawaannya. MP1584 disolder langsung (header male ±2,5 mm) karena ada di bawah dudukan baterai.
3. **Set MP1584 ke 5,0 V sebelum rangka/dudukan baterai dipasang** (trimpot tidak terjangkau setelahnya),
   dan sebelum ESP32 dicolok ke socket.
4. **OLED:** header di sisi depan, jadi tampilan sudah tegak dilihat dari belakang robot, **tidak perlu
   diputar** di firmware (U8g2: `U8G2_R0`). Urutan pin di PCB: GND, VCC, SCL, SDA (tertulis di silkscreen).
   Dari belakang, bagian belakang layar agak tertutup cover; paling jelas dilihat dari atas.
5. **PCB sensor:** ITR20001 di sisi BAWAH (menghadap lantai, diputar: kaki LED IR di depan), begitu juga
   pull-up 10k (di bawah modul mux) dan Q1/R41/R42. Sisi atas: LED indikator + resistornya, resistor LED IR di
   sela antar pasangan sensor, modul mux & MCP23017 di socket, J1. Nomor 1–16 di tepi depan = S1–S16.
   Pasang MCP23017 dengan takik ke kiri (pin 1 di belakang kiri) dan modul mux sesuai tulisan C0..C15.
6. **Baterai & saklar** ada di tepi kanan PCB utama: J1 di celah antara dudukan baterai dan tepi papan, saklar
   di depannya (tuas keluar ke kanan, di bawah OLED). J1: pin kotak = BAT+ (tanda `+`). Posisi ON saklar:
   cek dengan multimeter (pin tengah tersambung ke BAT+).
   **Ngecas tidak lewat PCB:** modul charger 2S USB-C ada di dinding belakang rangka (port menghadap
   belakang), OUT+/OUT− modul ke P+/P− BMS, P+/P− BMS ke J1. Bisa dicas saat saklar OFF. Detail kabel:
   `docs/skematik-v1.md` bagian Daya.
7. Area belakang (Y < 30 mm) ada di bawah plat dudukan baterai (ruang ±9,9 mm): MP1584 (tinggi ±8,1 mm),
   D1, R1/R2, dan konektor motor J2/J3 (JST PH tegak) ada di sini, cek colokan + kabelnya muat.
8. Antena ESP32 (ujung kanan modul): tanpa pour GND di kedua sisi. Jalur sinyal boleh lewat di bawahnya
   karena modul duduk di socket ±8,5 mm di atas PCB.
9. **BMS** ditempel di sisi bawah PCB utama di bagian kiri, di antara dua baris kaki socket ESP32 (ada kotak
   silkscreen bawah); tidak ada kaki solder di area itu.

### Disamakan dengan model mekanik

Kedua PCB = model `arsip/mechanical/cadquery/ltm_v12.py` (13/10/2026). Lubang bahu H3/H4 di (±37,5; 69) dan lubang
H1/H2 PCB sensor di (±52; 92,5) dipakai lengan dudukan; konektor motor di X ±(17–27) mm. Di sisi bawah PCB
utama ada tanda tempat **ball caster** (0; 62), area itu sengaja bebas kaki solder, dan tanda tempat **BMS**.
Di model v12 tepi depan dudukan baterai dimundurkan ke Y 29,5 (ESP32 mulai Y 30,2).

## Checklist sebelum pesan PCB

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
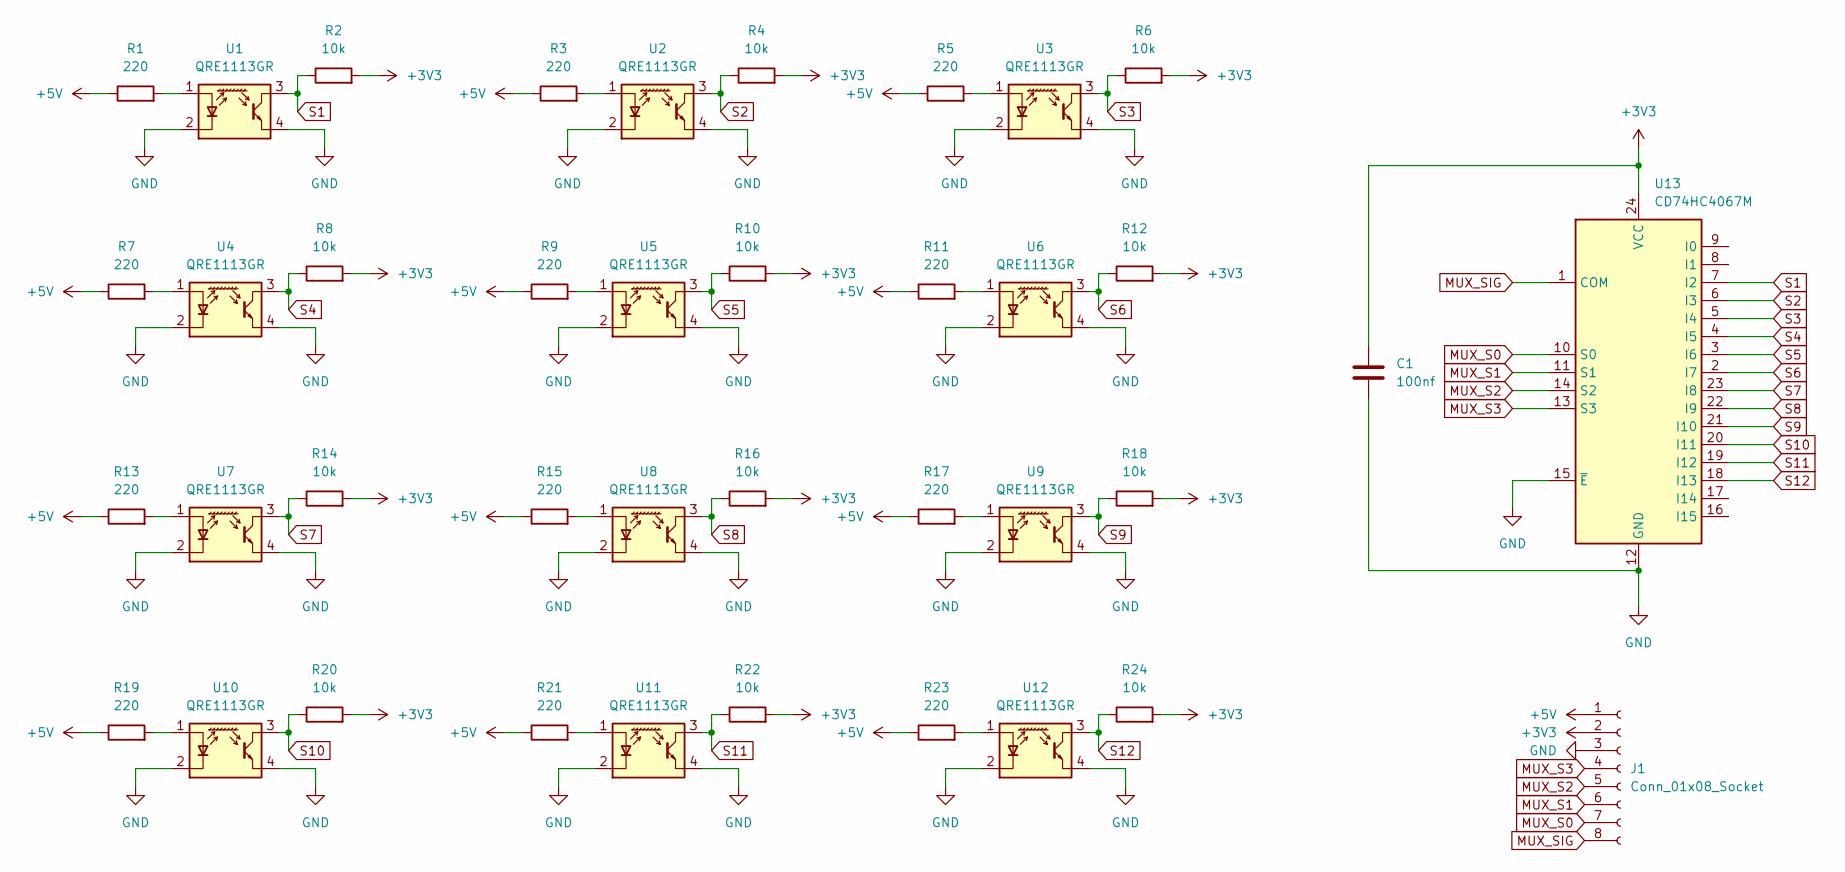
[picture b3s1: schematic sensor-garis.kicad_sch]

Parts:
C1: 100nf; C_0805_2012Metric_Pad1.18x1.45mm_HandSolder
J1: Conn_01x08_Socket; JST_XH_B8B-XH-A_1x08_P2.50mm_Vertical
R1, R3, R5, R7, R9, R11, R13, R15, R17, R19, R21, R23: 220; R_0805_2012Metric_Pad1.20x1.40mm_HandSolder
R2, R4, R6, R8, R10, R12, R14, R16, R18, R20, R22, R24: 10k; R_0805_2012Metric_Pad1.20x1.40mm_HandSolder
U1, U2, U3, U4, U5, U6, U7, U8, U9, U10, U11, U12: QRE1113GR; OnSemi_CASE100CY
U13: CD74HC4067M; SOIC-24W_7.5x15.4mm_P1.27mm

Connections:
+3V3: C1.1, J1.2, R2.2, R4.2, R6.2, R8.2, R10.2, R12.2, R14.2, R16.2, R18.2, R20.2, R22.2, R24.2, U13.24 (VCC)
+5V: J1.1, R1.1, R3.1, R5.1, R7.1, R9.1, R11.1, R13.1, R15.1, R17.1, R19.1, R21.1, R23.1
GND: C1.2, J1.3, U1.2 (K), U1.4, U2.2 (K), U2.4, U3.2 (K), U3.4, U4.2 (K), U4.4, U5.2 (K), U5.4, U6.2 (K), U6.4, U7.2 (K), U7.4, U8.2 (K), U8.4, U9.2 (K), U9.4, U10.2 (K), U10.4, U11.2 (K), U11.4, U12.2 (K), U12.4, U13.12 (GND), U13.15 (~E)
MUX_S0: J1.7, U13.10 (S0)
MUX_S1: J1.6, U13.11 (S1)
MUX_S2: J1.5, U13.14 (S2)
MUX_S3: J1.4, U13.13 (S3)
MUX_SIG: J1.8, U13.1 (COM)
unnamed: R1.2, U1.1 (A)
unnamed: R3.2, U2.1 (A)
unnamed: R5.2, U3.1 (A)
unnamed: R7.2, U4.1 (A)
unnamed: R9.2, U5.1 (A)
unnamed: R11.2, U6.1 (A)
unnamed: R13.2, U7.1 (A)
unnamed: R15.2, U8.1 (A)
unnamed: R17.2, U9.1 (A)
unnamed: R19.2, U10.1 (A)
unnamed: R21.2, U11.1 (A)
unnamed: R23.2, U12.1 (A)
S1: R2.1, U1.3, U13.7 (I2)
S2: R4.1, U2.3, U13.6 (I3)
S3: R6.1, U3.3, U13.5 (I4)
S4: R8.1, U4.3, U13.4 (I5)
S5: R10.1, U5.3, U13.3 (I6)
S6: R12.1, U6.3, U13.2 (I7)
S7: R14.1, U7.3, U13.23 (I8)
S8: R16.1, U8.3, U13.22 (I9)
S9: R18.1, U9.3, U13.21 (I10)
S10: R20.1, U10.3, U13.20 (I11)
S11: R22.1, U11.3, U13.19 (I12)
S12: R24.1, U12.3, U13.18 (I13)

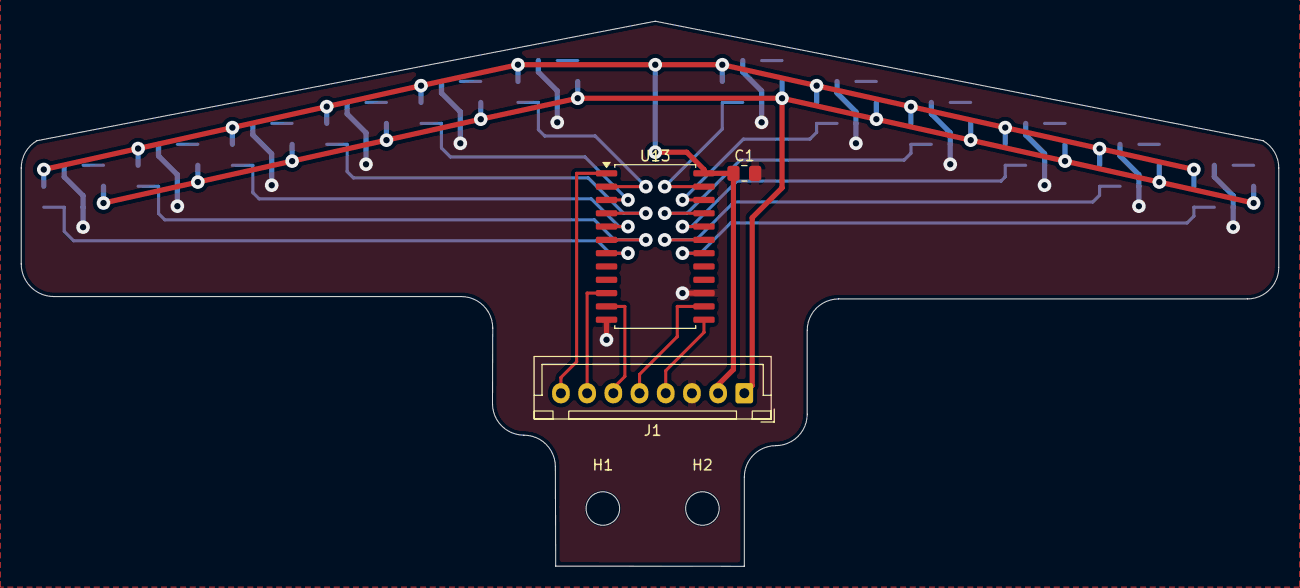
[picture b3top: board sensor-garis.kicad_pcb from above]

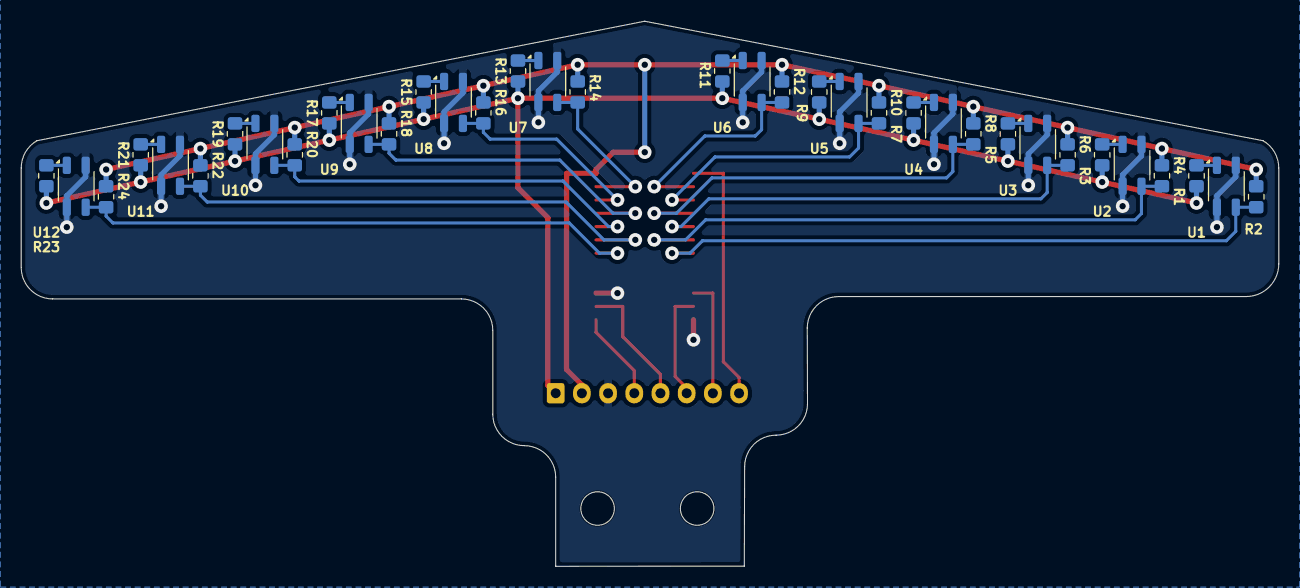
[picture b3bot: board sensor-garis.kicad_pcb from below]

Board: 2 copper layers, 120.0 x 52.0 mm, 41 parts (36 on the bottom side), 32 nets.

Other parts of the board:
H1, H2: MountingHole; MountingHole_3.2mm_M3
